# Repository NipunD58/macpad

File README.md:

# Nipun's Macpad
First time with PCB and CAD, pls don't judge
made this for hackclub blueprint <3

### Inspiration

I wanted to create a macropad that helps me to be more productive. I created a Macropad using 4 switches, 1 rp2040, and 2 leds. 

### Challenges
Fusion 360 was very hard to use as a beginner. It took most of my time to make the MacPad
### Specifications

BOM: 
- 4x Cherry MX Switches
- 3x SK6812 MINI Leds
- 1x XIAO RP2040
- 4x Blank DSA Keycaps
- 4x M3x16 Bolt
- 4x M3 Heatset

Others:
- KMK Firmware
- Top Case.stl 
- Bottom Case.stl

Schematic            |  PCB         |   Case
:-------------------------:|:-------------------------:|:-------------------------:|
![image](

)  | ![image](
)

![image](
/>

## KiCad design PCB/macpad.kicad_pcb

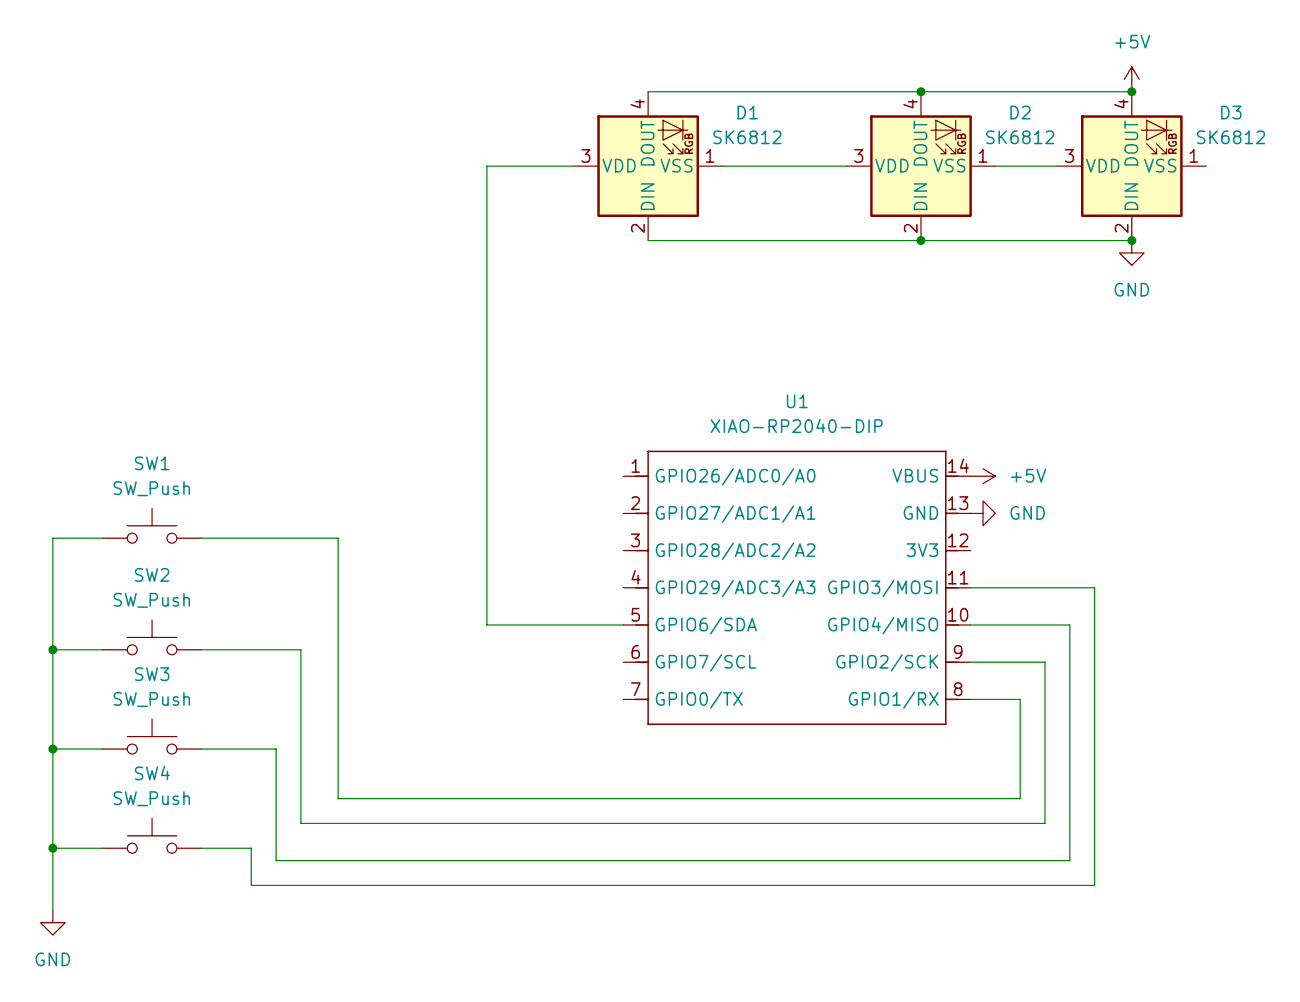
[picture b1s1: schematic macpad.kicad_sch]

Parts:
D1, D2, D3: SK6812; LED_SK6812_PLCC4_5.0x5.0mm_P3.2mm
SW1, SW2, SW3, SW4: SW_Push; SW_Cherry_MX_1.00u_PCB
U1: XIAO-RP2040-DIP; XIAO-ESP32C3-DIP

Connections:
+5V: D1.4 (DOUT), D2.4 (DOUT), D3.4 (DOUT), U1.14 (VBUS)
GND: D1.2 (DIN), D2.2 (DIN), D3.2 (DIN), SW1.1, SW2.1, SW3.1, SW4.1, U1.13 (GND)
unnamed: D1.3 (VDD), U1.5 (GPIO6/SDA)
unnamed: D1.1 (VSS), D2.3 (VDD)
unnamed: D2.1 (VSS), D3.3 (VDD)
unnamed: SW1.2, U1.8 (GPIO1/RX)
unnamed: SW2.2, U1.9 (GPIO2/SCK)
unnamed: SW4.2, U1.11 (GPIO3/MOSI)
unnamed: SW3.2, U1.10 (GPIO4/MISO)

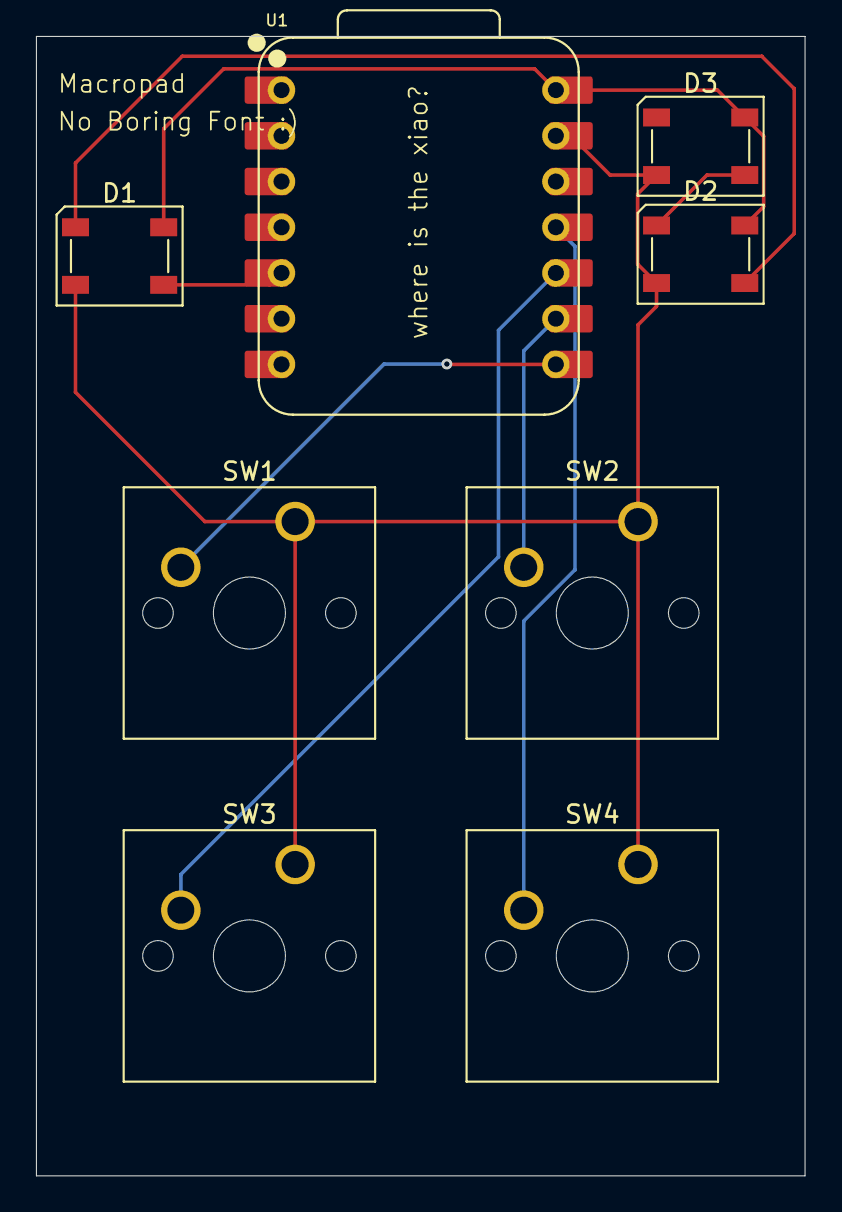
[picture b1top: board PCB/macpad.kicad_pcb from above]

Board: 2 copper layers, 42.7 x 63.3 mm, 8 parts (0 on the bottom side), 9 nets.

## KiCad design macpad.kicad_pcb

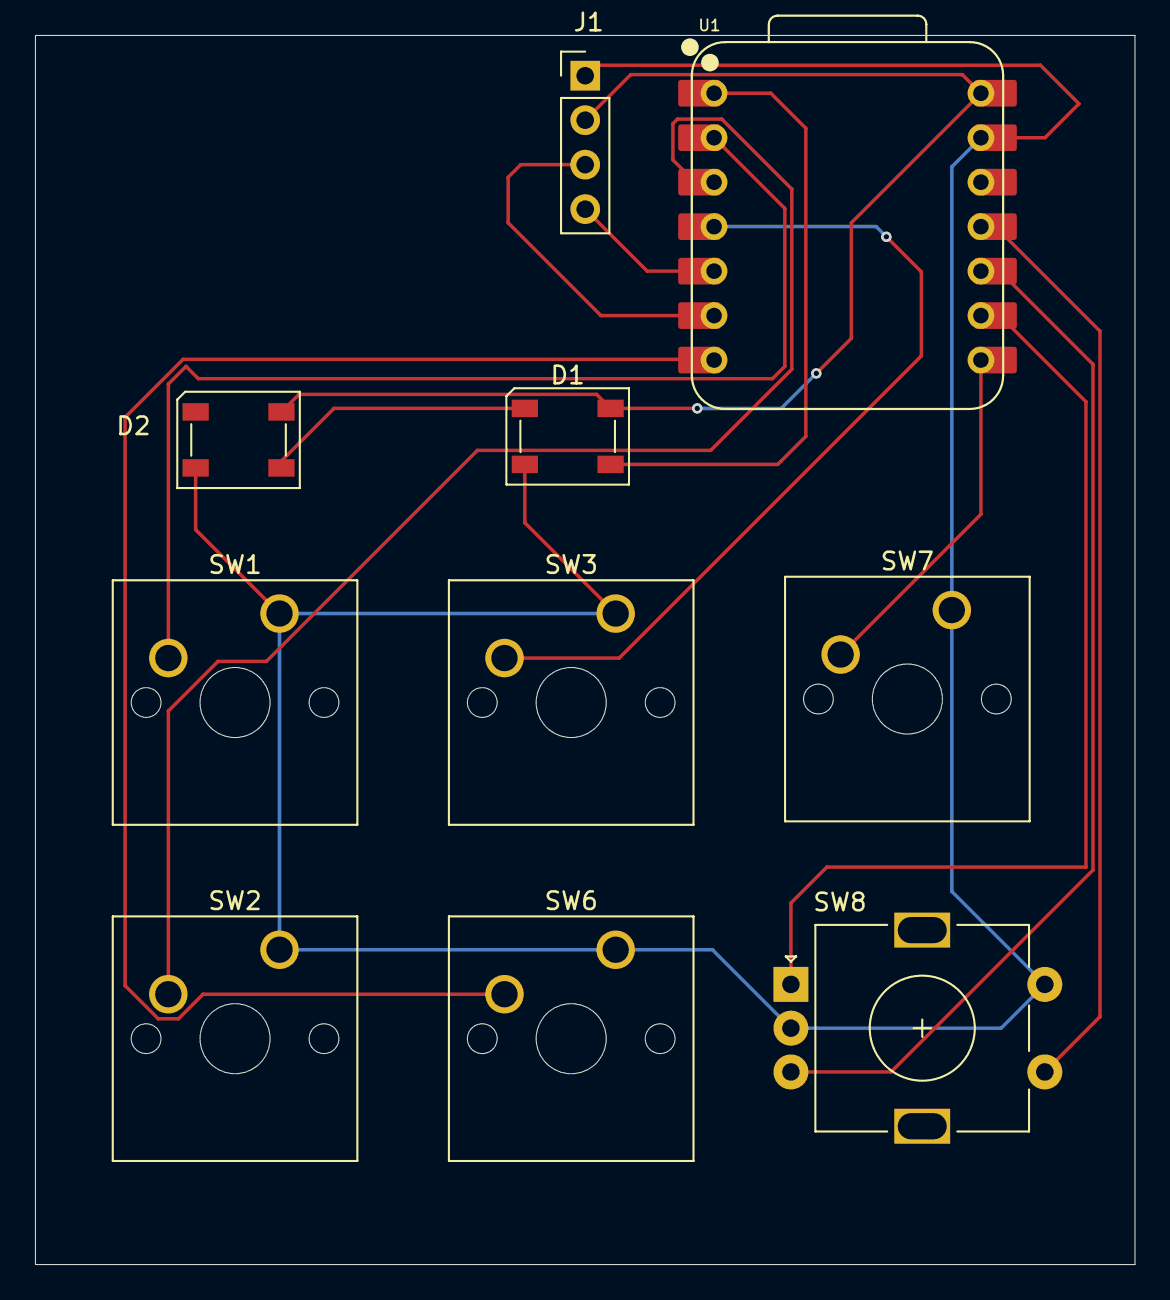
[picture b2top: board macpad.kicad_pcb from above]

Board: 2 copper layers, 62.8 x 70.2 mm, 10 parts (0 on the bottom side), 14 nets.

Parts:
D1, D2: SK6812; LED_SK6812_PLCC4_5.0x5.0mm_P3.2mm
J1: Conn_01x04_Pin; PinHeader_1x04_P2.54mm_Vertical
SW1, SW2, SW3, SW6, SW7: SW_Push; SW_Cherry_MX_1.00u_PCB
SW8: RotaryEncoder_Switch; RotaryEncoder_Alps_EC11E-Switch_Vertical_H20mm
U1: XIAO-RP2040-DIP; XIAO-ESP32C3-DIP

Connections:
+5V: D1.4 (DOUT), D2.4 (DOUT), J1.2, U1.14 (VBUS)
GND: D1.2 (DIN), D2.2 (DIN), J1.1, SW1.1, SW2.1, SW3.1, SW6.1, SW7.1, SW8.C, SW8.S2, U1.13 (GND)
unnamed: D1.3 (VDD), U1.1 (GPIO26/ADC0/A0)
unnamed: D1.1 (VSS), D2.3 (VDD)
unnamed: SW6.2, U1.7 (GPIO0/TX)
unnamed: SW7.2, U1.8 (GPIO1/RX)
unnamed: SW8.A, U1.9 (GPIO2/SCK)
unnamed: SW8.S1, U1.11 (GPIO3/MOSI)
unnamed: SW8.B, U1.10 (GPIO4/MISO)
unnamed: SW1.2, U1.2 (GPIO27/ADC1/A1)
unnamed: SW2.2, U1.3 (GPIO28/ADC2/A2)
unnamed: SW3.2, U1.4 (GPIO29/ADC3/A3)
SCL: J1.3, U1.6 (GPIO7/SCL)
SDA: J1.4, U1.5 (GPIO6/SDA)

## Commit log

2025-11-16 Update README for clarity and corrections
    Corrected grammar and capitalization in README.
2026-02-06 Initial plan
2026-02-06 Add Arduino firmware with VC-02 module code removed, using touch sensor cycles only
2026-02-06 Fix misleading comments in firmware identified by code review
2026-02-06 Remove pulse verification from touch sensor and use simple digitalRead detection
    - Remove PULSE_VERIFY_DELAY and PULSE_VERIFY_COUNT constants
    - Remove verifyPulse() function
    - Simplify checkTouchSensor() to trigger directly on HIGH
    - Add delay(500) in main loop for debouncing
    - Update Serial prints to match reference code style
